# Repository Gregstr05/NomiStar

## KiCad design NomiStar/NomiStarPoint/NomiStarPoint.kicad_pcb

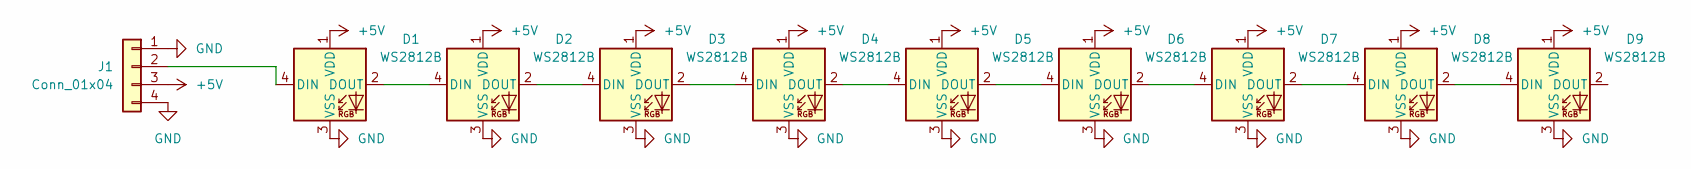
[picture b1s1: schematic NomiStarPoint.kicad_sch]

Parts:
D1, D2, D3, D4, D5, D6, D7, D8, D9: WS2812B; LED_WS2812B_PLCC4_5.0x5.0mm_P3.2mm
J1: Conn_01x04; PinHeader_1x04_P2.54mm_Vertical

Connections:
+5V: D1.1 (VDD), D2.1 (VDD), D3.1 (VDD), D4.1 (VDD), D5.1 (VDD), D6.1 (VDD), D7.1 (VDD), D8.1 (VDD), D9.1 (VDD), J1.3
GND: D1.3 (VSS), D2.3 (VSS), D3.3 (VSS), D4.3 (VSS), D5.3 (VSS), D6.3 (VSS), D7.3 (VSS), D8.3 (VSS), D9.3 (VSS), J1.1, J1.4
unnamed: D1.4 (DIN), J1.2
unnamed: D1.2 (DOUT), D2.4 (DIN)
unnamed: D2.2 (DOUT), D3.4 (DIN)
unnamed: D3.2 (DOUT), D4.4 (DIN)
unnamed: D4.2 (DOUT), D5.4 (DIN)
unnamed: D5.2 (DOUT), D6.4 (DIN)
unnamed: D6.2 (DOUT), D7.4 (DIN)
unnamed: D7.2 (DOUT), D8.4 (DIN)
unnamed: D8.2 (DOUT), D9.4 (DIN)

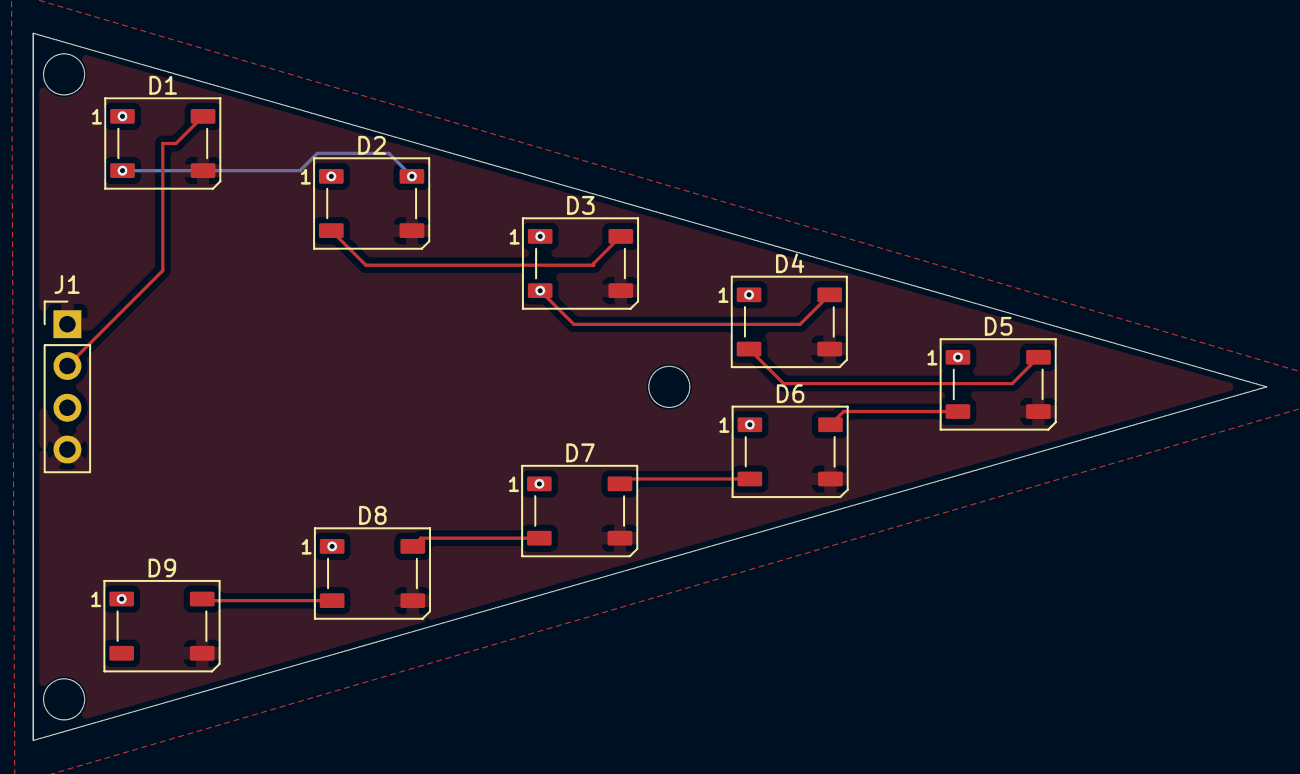
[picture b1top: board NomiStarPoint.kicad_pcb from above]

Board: 2 copper layers, 75.0 x 43.0 mm, 10 parts (0 on the bottom side), 11 nets.

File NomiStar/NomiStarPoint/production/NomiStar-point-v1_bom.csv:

Designator,Footprint,Quantity,Value,LCSC Part #
"D1, D2, D3, D4, D5, D6, D7, D8, D9",LED_WS2812B_PLCC4_5.0x5.0mm_P3.2mm,9,WS2812B,
J1,PinHeader_1x04_P2.54mm_Vertical,1,Conn_01x04,

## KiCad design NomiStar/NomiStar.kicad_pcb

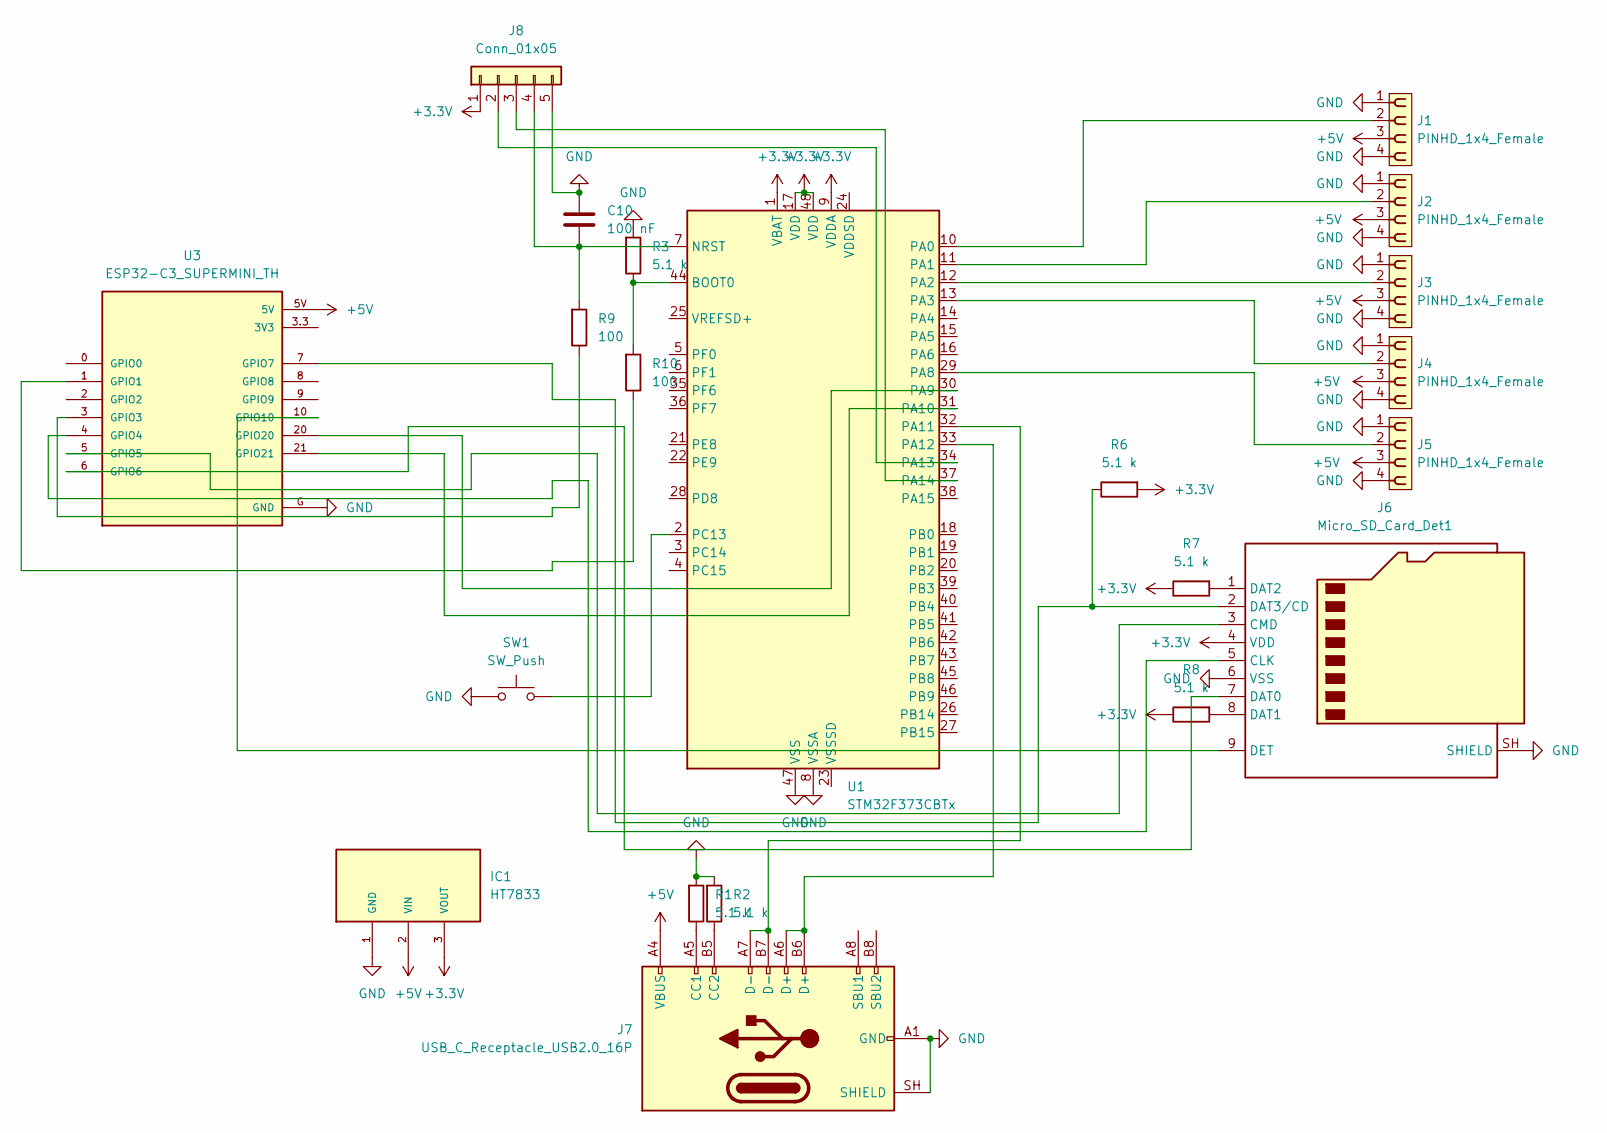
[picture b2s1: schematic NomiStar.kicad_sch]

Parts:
C10: 100 nF; C_0603_1608Metric
IC1: HT7833
J1, J2, J3, J4, J5: PINHD_1x4_Female; PinSocket_1x04_P2.54mm_Vertical
J6: Micro_SD_Card_Det1; microSD_HC_Molex_104031-0811
J7: USB_C_Receptacle_USB2.0_16P; USB_C_Receptacle_GCT_USB4105-xx-A_16P_TopMnt_Horizontal
J8: Conn_01x05; PinHeader_1x05_P2.54mm_Vertical
R1, R2, R3, R6, R7, R8: 5.1 k; R_0603_1608Metric
R9, R10: 100; R_0603_1608Metric
SW1: SW_Push; SW_Push_SPST_NO_Alps_SKRK
U1: STM32F373CBTx; LQFP-48_7x7mm_P0.5mm
U3: ESP32-C3_SUPERMINI_TH; MODULE_ESP32-C3_SUPERMINI_TH

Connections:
+3.3V: IC1.3 (VOUT), J6.4 (VDD), J8.1, R6.1, R7.2, R8.2, U1.1 (VBAT), U1.9 (VDDA), U1.17 (VDD), U1.48 (VDD)
+5V: IC1.2 (VIN), IC1.2@1 (VIN), J1.3, J2.3, J3.3, J4.3, J5.3, J7.A4 (VBUS), J7.A9 (VBUS), J7.B4 (VBUS), J7.B9 (VBUS), U3.5V
GND: C10.1, IC1.1 (GND), J1.1, J1.4, J2.1, J2.4, J3.1, J3.4, J4.1, J4.4, J5.1, J5.4, J6.6 (VSS), J6.SH (SHIELD), J7.A1 (GND), J7.A12 (GND), J7.B1 (GND), J7.B12 (GND), J7.SH (SHIELD), J8.5, R1.1, R2.1, R3.1, SW1.1, U1.8 (VSSA), U1.47 (VSS), U3.G (GND)
unnamed: J6.5 (CLK), U3.4 (GPIO4)
unnamed: J6.3 (CMD), U3.5 (GPIO5)
unnamed: J6.7 (DAT0), U3.6 (GPIO6)
unnamed: J6.8 (DAT1), R8.1
unnamed: J6.1 (DAT2), R7.1
unnamed: J6.2 (DAT3/CD), R6.2, U3.7 (GPIO7)
unnamed: J6.9 (DET), U3.10 (GPIO10)
unnamed: J7.A5 (CC1), R1.2
unnamed: J7.B5 (CC2), R2.2
unnamed: J8.2, U1.34 (PA13)
unnamed: J8.3, U1.37 (PA14)
unnamed: C10.2, J8.4, R9.1, U1.7 (NRST)
unnamed: R3.2, R10.1, U1.44 (BOOT0)
unnamed: J1.2, U1.10 (PA0)
unnamed: J2.2, U1.11 (PA1)
unnamed: J3.2, U1.12 (PA2)
unnamed: J4.2, U1.13 (PA3)
unnamed: J5.2, U1.29 (PA8)
unnamed: U1.30 (PA9), U3.20 (GPIO20)
unnamed: U1.31 (PA10), U3.21 (GPIO21)
unnamed: J7.A7 (D-), J7.B7 (D-), U1.32 (PA11)
unnamed: J7.A6 (D+), J7.B6 (D+), U1.33 (PA12)
unnamed: SW1.2, U1.2 (PC13)
unnamed: R10.2, U3.1 (GPIO1)
unnamed: R9.2, U3.3 (GPIO3)

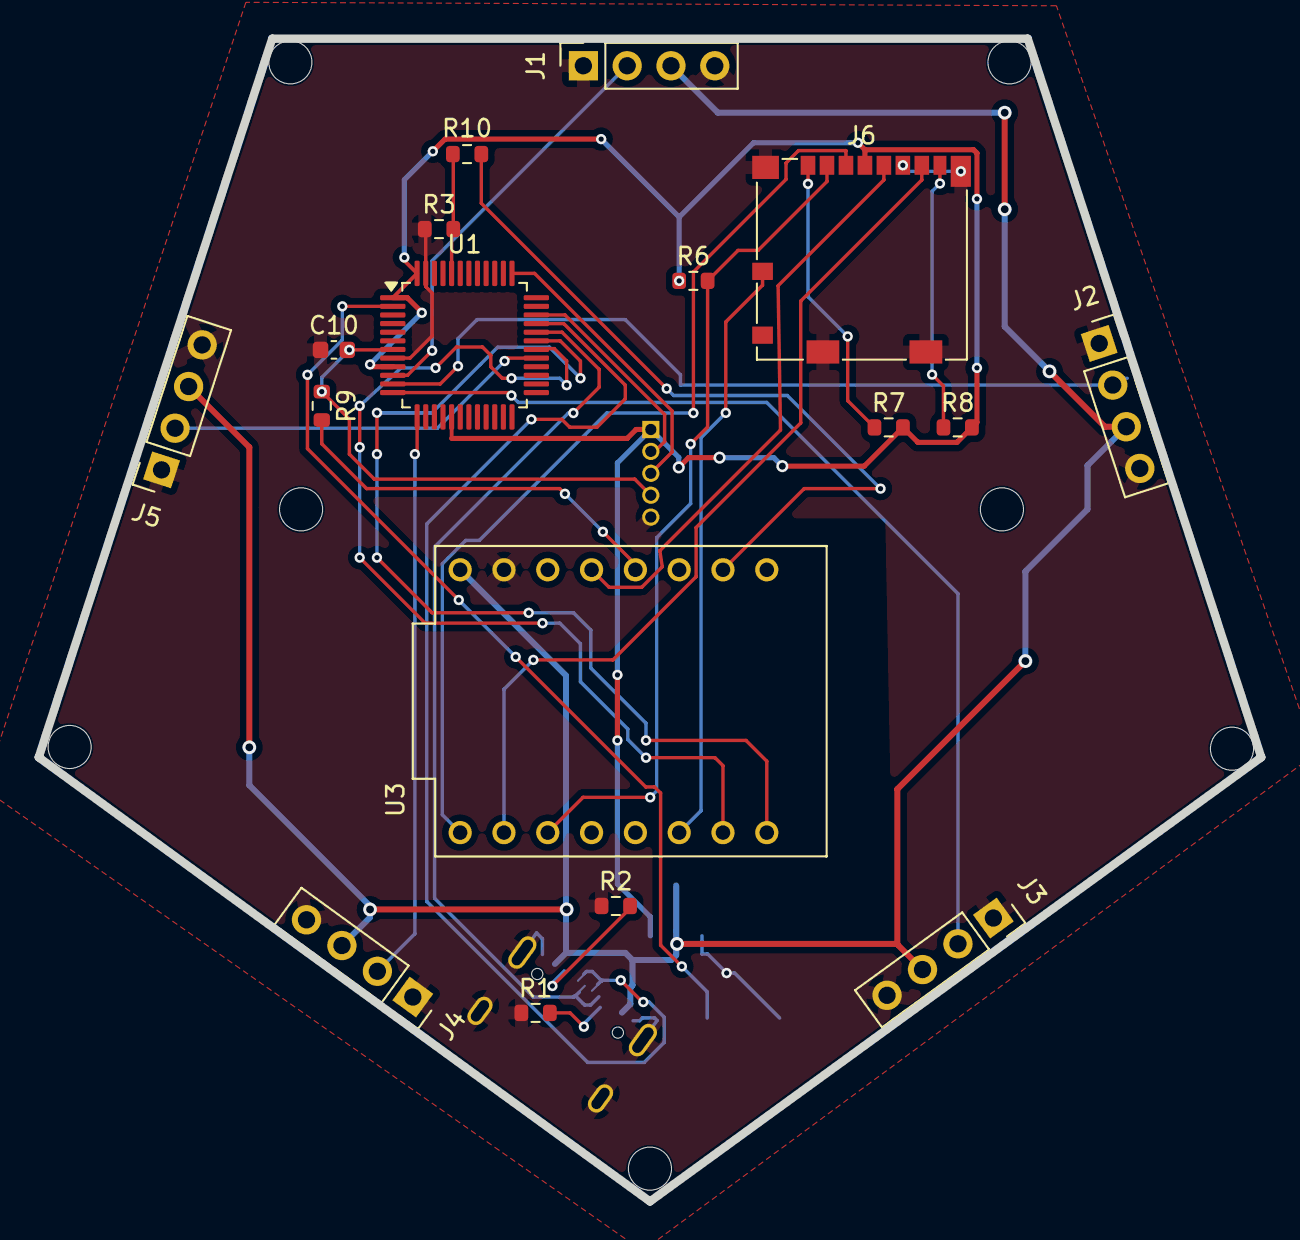
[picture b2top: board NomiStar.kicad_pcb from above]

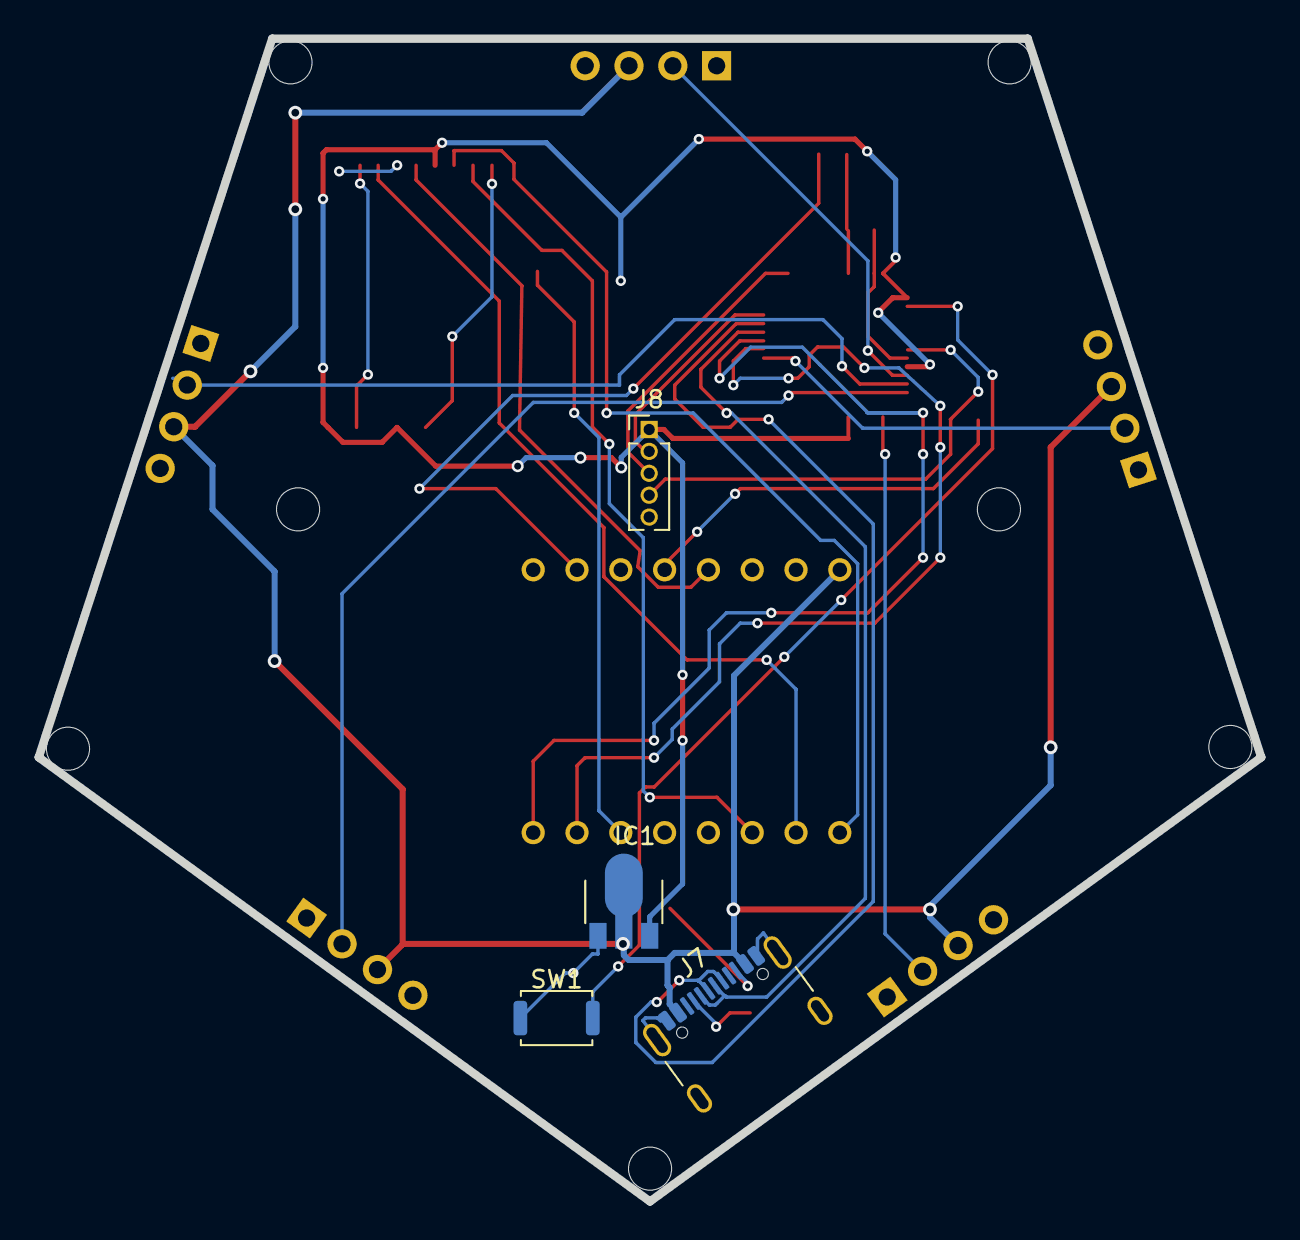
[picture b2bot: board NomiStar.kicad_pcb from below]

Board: 2 copper layers, 70.9 x 67.4 mm, 21 parts (4 on the bottom side), 28 nets.
